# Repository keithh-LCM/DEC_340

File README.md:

Mostly eagle files, an xtra folder has extra documents.

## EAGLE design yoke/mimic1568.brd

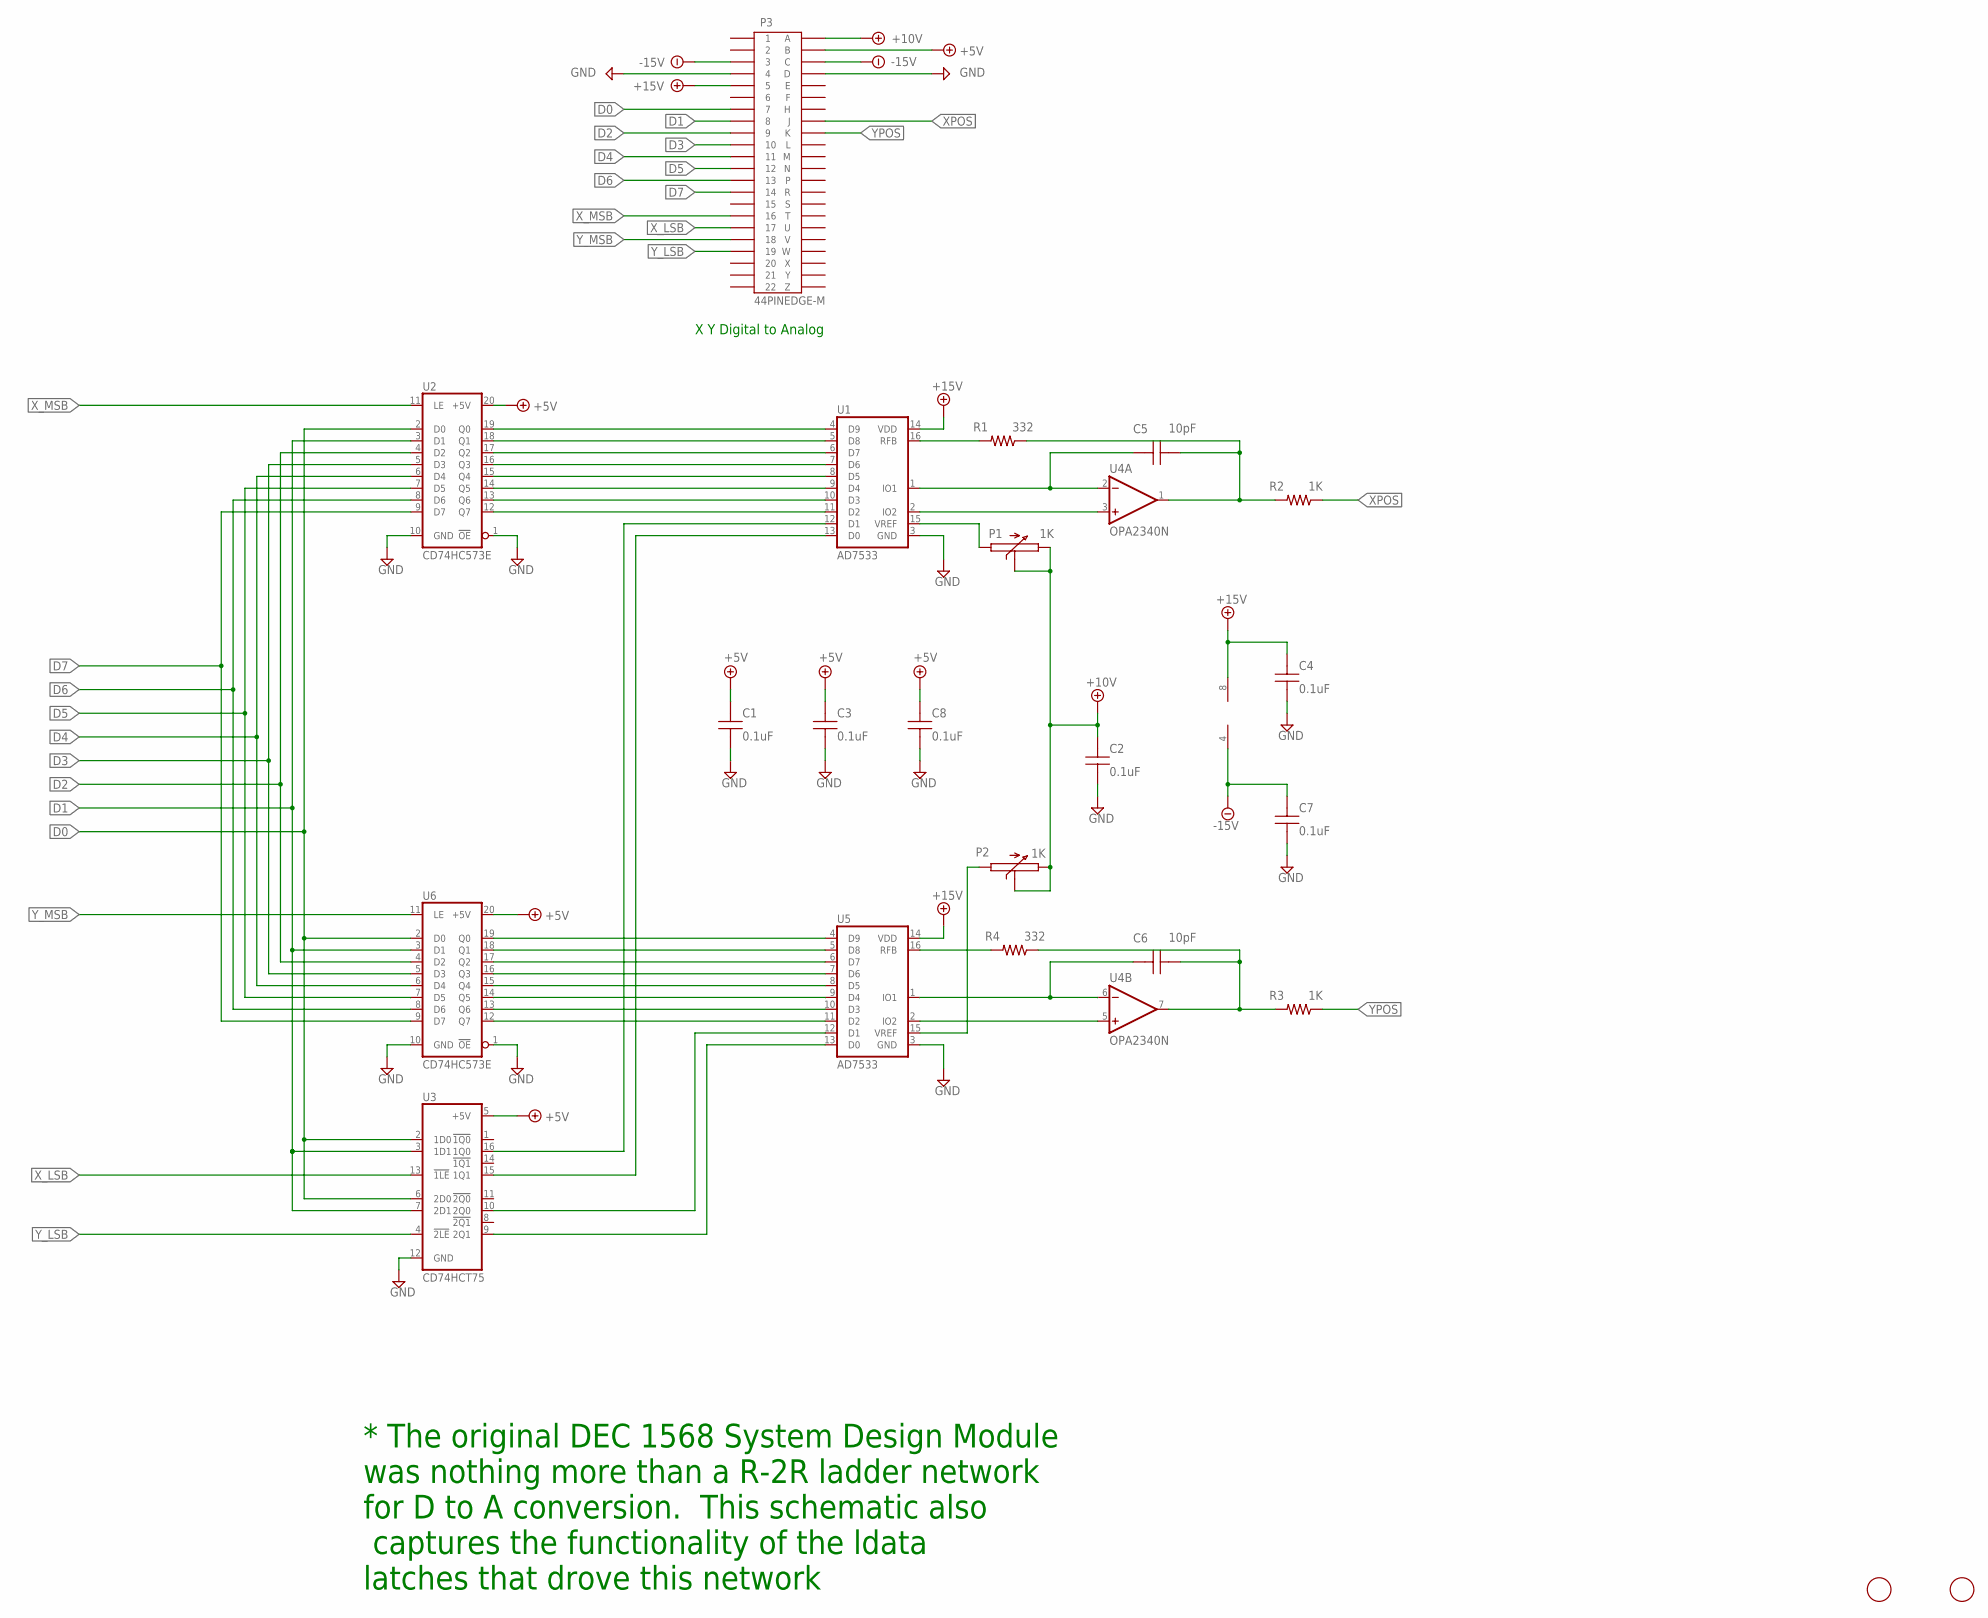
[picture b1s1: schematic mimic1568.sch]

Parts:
C1, C2, C3, C4, C7, C8: 0.1uF; 5MM_TH
C5, C6: 10pF; 5MM_TH
P1, P2: 1K; 3006P
P3: 44PINEDGE-M; 44PINEDGE
R1, R4: 332; 0207/10
R2, R3: 1K; 0207/10
U1, U5: AD7533; DIP-16
U2, U6: CD74HC573E; DIP-20
U3: CD74HCT75; DIP-16
U4: OPA2340N; DIP-08
U$1, U$2: FIDUCIAL; FIDUCIAL_1MM

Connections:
+5V: C1.1, C3.1, C8.1, P3.B, U2.20 (+5V), U3.5 (+5V), U6.20 (+5V)
+10V: C2.1, P1.2, P1.3, P2.2, P2.3, P3.A
+15V: C4.1, P3.5, U1.14 (VDD), U4.8 (V+), U5.14 (VDD)
-15V: C7.1, P3.3, P3.C, U4.4 (V-)
D0: P3.7, U2.2 (D0), U3.2 (1D0), U3.6 (2D0), U6.2 (D0)
D1: P3.8, U2.3 (D1), U3.3 (1D1), U3.7 (2D1), U6.3 (D1)
D2: P3.9, U2.4 (D2), U6.4 (D2)
D3: P3.10, U2.5 (D3), U6.5 (D3)
D4: P3.11, U2.6 (D4), U6.6 (D4)
D5: P3.12, U2.7 (D5), U6.7 (D5)
D6: P3.13, U2.8 (D6), U6.8 (D6)
D7: P3.14, U2.9 (D7), U6.9 (D7)
GND: C1.2, C2.2, C3.2, C4.2, C7.2, C8.2, P3.4, P3.D, U1.3 (GND), U2.1 (!OE), U2.10 (GND), U3.12 (GND), U5.3 (GND), U6.1 (!OE), U6.10 (GND)
unnamed: U3.9 (2Q1), U5.13 (D0)
unnamed: R4.2, U5.16 (RFB)
unnamed: U1.12 (D1), U3.16 (1Q0)
unnamed: U1.13 (D0), U3.15 (1Q1)
unnamed: C5.1, U1.1 (IO1), U4.2 (-IN)
unnamed: U1.2 (IO2), U4.3 (+IN)
unnamed: U5.4 (D9), U6.19 (Q0)
unnamed: U5.5 (D8), U6.18 (Q1)
unnamed: U5.6 (D7), U6.17 (Q2)
unnamed: U5.7 (D6), U6.16 (Q3)
unnamed: U5.8 (D5), U6.15 (Q4)
unnamed: U5.9 (D4), U6.14 (Q5)
unnamed: U5.10 (D3), U6.13 (Q6)
unnamed: U5.11 (D2), U6.12 (Q7)
unnamed: C5.2, R1.1, R2.2, U4.1 (OUT)
unnamed: P1.1, U1.15 (VREF)
unnamed: U1.4 (D9), U2.19 (Q0)
unnamed: U1.5 (D8), U2.18 (Q1)
unnamed: U1.6 (D7), U2.17 (Q2)
unnamed: U1.7 (D6), U2.16 (Q3)
unnamed: U1.8 (D5), U2.15 (Q4)
unnamed: U1.9 (D4), U2.14 (Q5)
unnamed: U1.10 (D3), U2.13 (Q6)
unnamed: U1.11 (D2), U2.12 (Q7)
unnamed: U3.10 (2Q0), U5.12 (D1)
unnamed: R1.2, U1.16 (RFB)
unnamed: C6.2, R3.2, R4.1, U4.7 (OUT)
unnamed: C6.1, U4.6 (-IN), U5.1 (IO1)
unnamed: U4.5 (+IN), U5.2 (IO2)
unnamed: P2.1, U5.15 (VREF)
XPOS: P3.J, R2.1
X_LSB: P3.17, U3.13 (!1LE)
X_MSB: P3.16, U2.11 (LE)
YPOS: P3.K, R3.1
Y_LSB: P3.19, U3.4 (!2LE)
Y_MSB: P3.18, U6.11 (LE)

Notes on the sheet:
* The original DEC 1568 System Design Module was nothing more than a R-2R ladder network for D to A conversion. This schematic also captures the functionality of the ldata latches that drove this network
X Y Digital to Analog

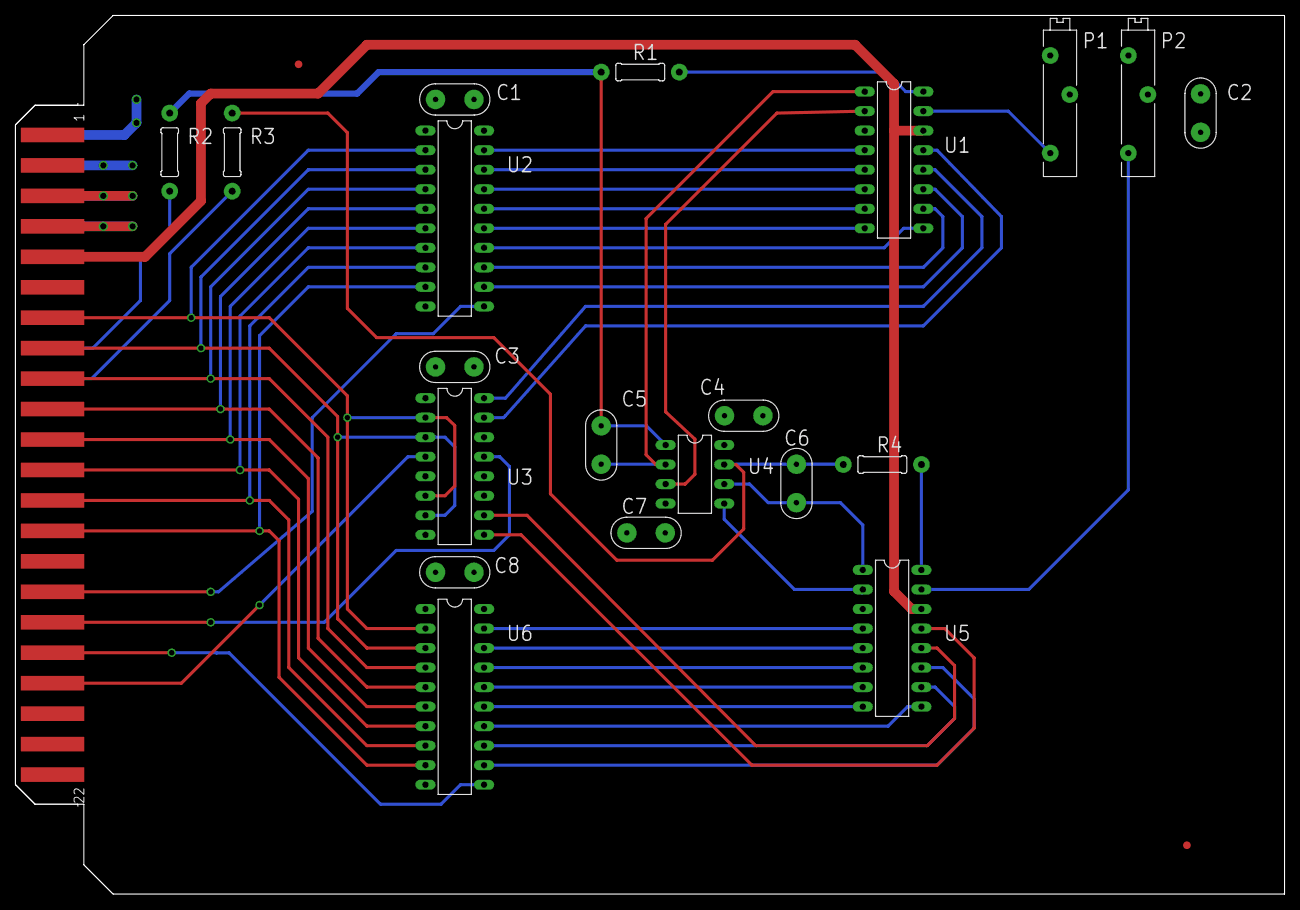
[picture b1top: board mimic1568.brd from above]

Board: 4 copper layers, 165.1 x 114.3 mm, 23 parts (0 on the bottom side), 49 nets.

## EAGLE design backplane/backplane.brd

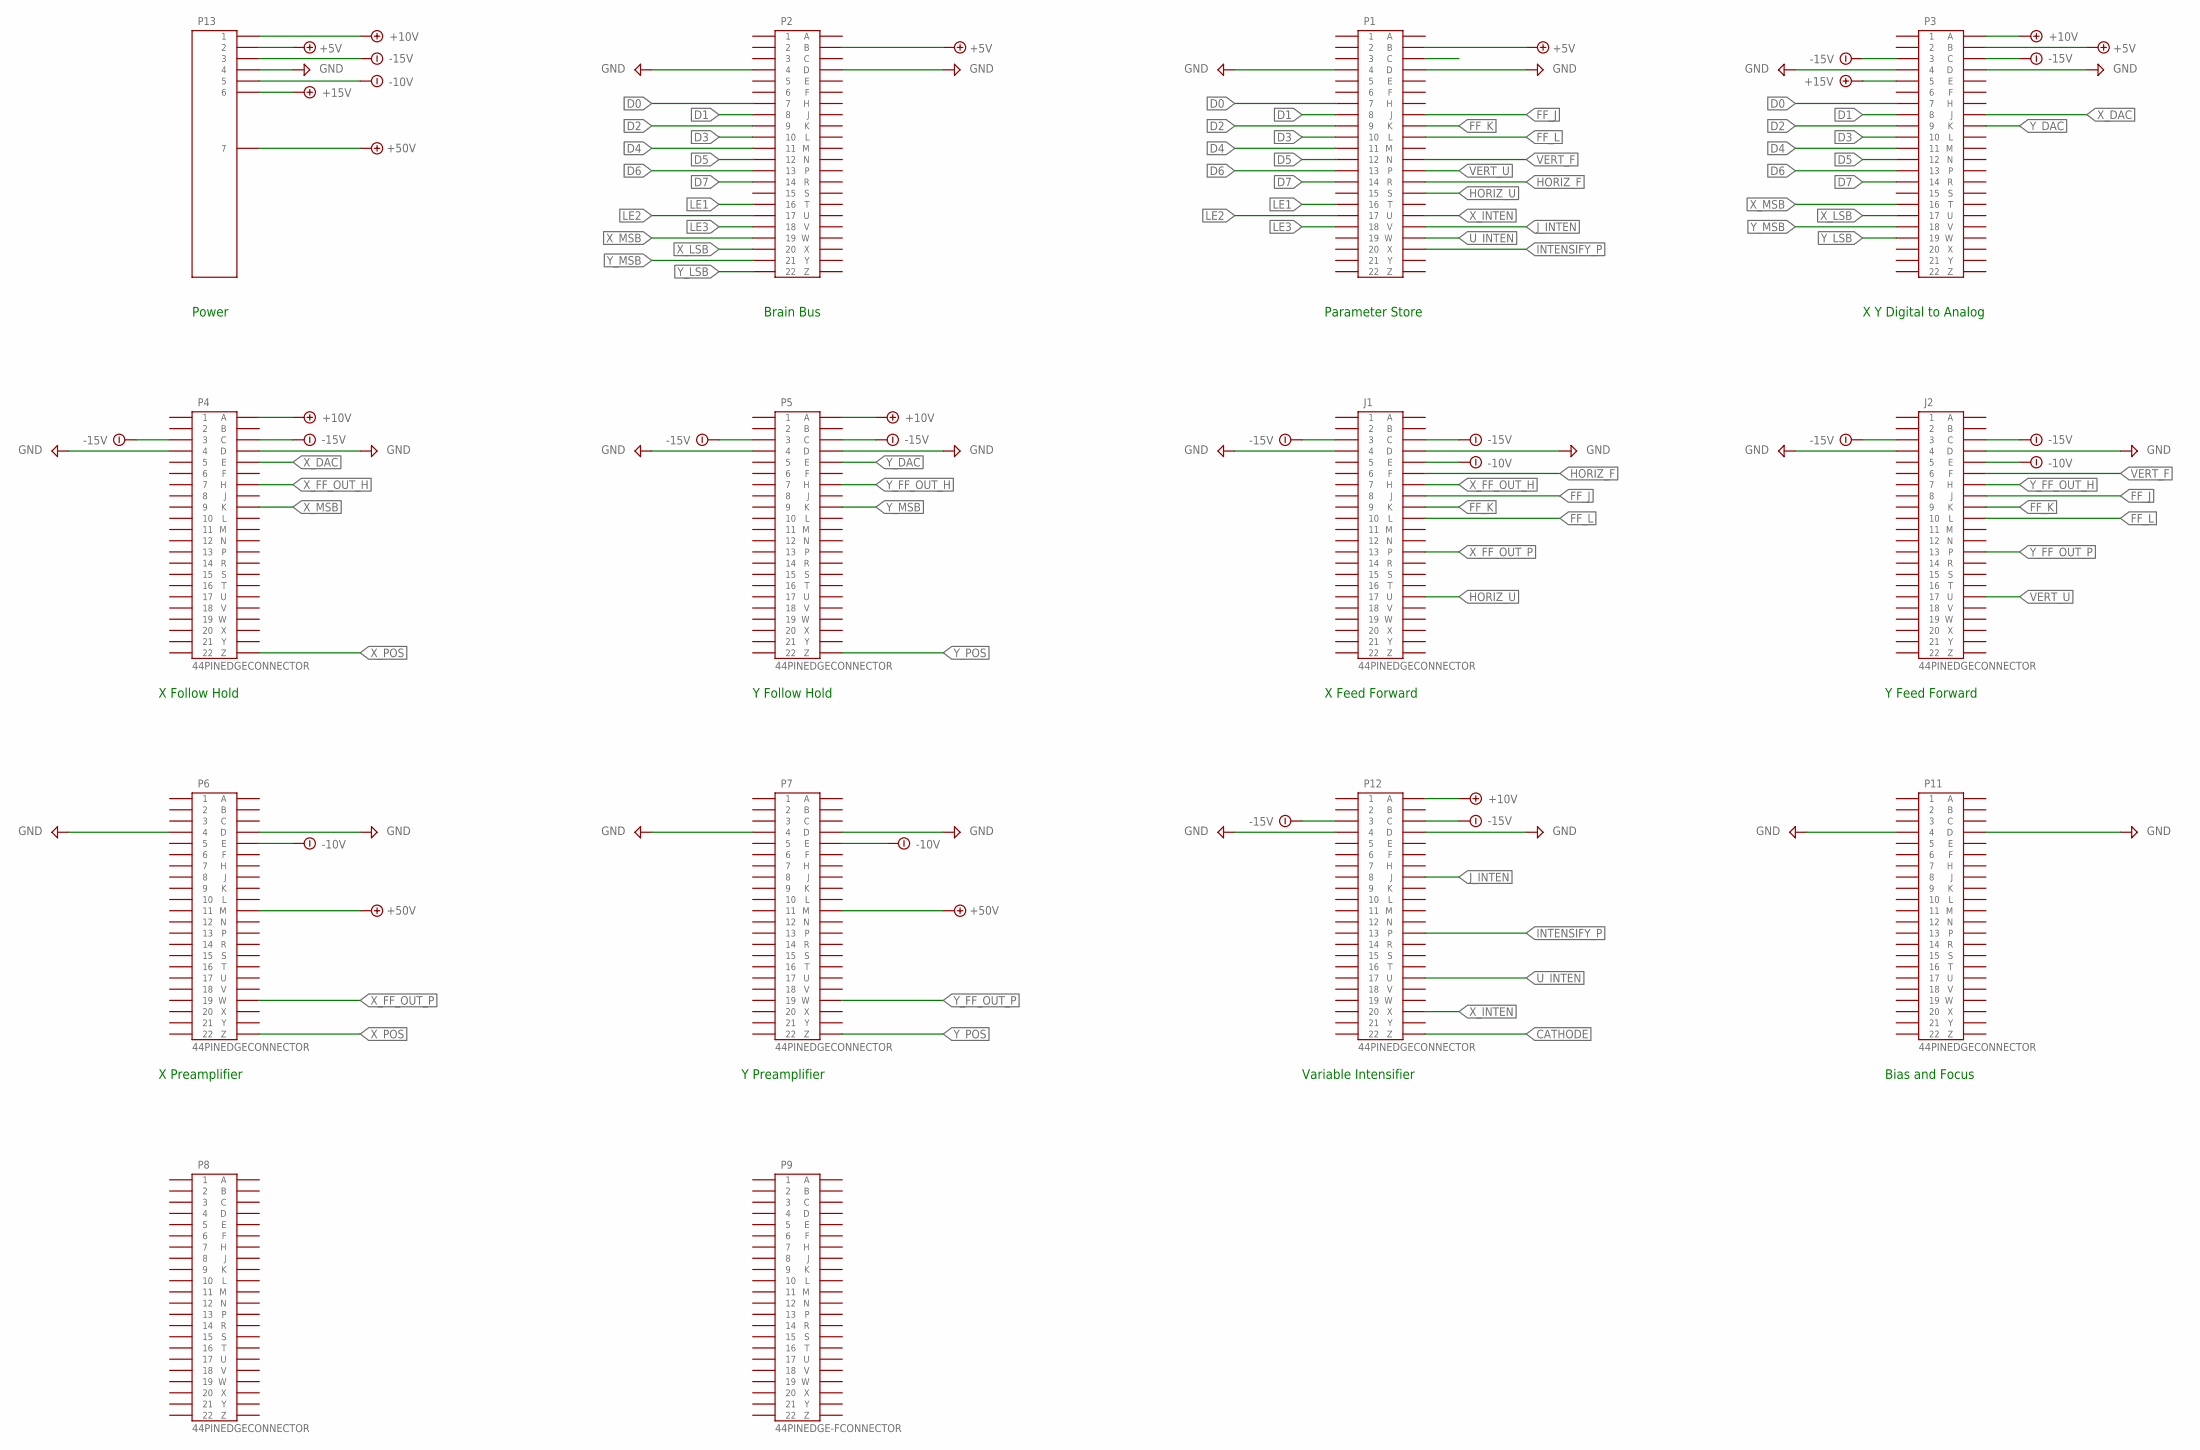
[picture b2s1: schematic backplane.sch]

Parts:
J1, J2: 44PINEDGECONNECTOR; 44PINEDGECONN
P1, P2, P3, P4, P5, P6, P7, P8, P11, P12: 44PINEDGECONNECTOR; 44PINEDGECONN
P9: 44PINEDGE-FCONNECTOR; 44PINEDGECONN
P13: PASSTHROUGH

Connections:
+5V: P1.P$24 (B), P2.P$24 (B), P3.P$24 (B), P13.P$2 (2)
+10V: P3.P$23 (A), P4.P$23 (A), P5.P$23 (A), P12.P$23 (A), P13.P$1 (1)
+15V: P3.P$5 (5), P13.P$6 (6)
+50V: P6.P$33 (M), P7.P$33 (M), P13.P$7 (7)
-10V: J1.P$27 (E), J2.P$27 (E), P6.P$27 (E), P7.P$27 (E), P13.P$5 (5)
-15V: J1.P$3 (3), J1.P$25 (C), J2.P$3 (3), J2.P$25 (C), P3.P$3 (3), P3.P$25 (C), P4.P$3 (3), P4.P$25 (C), P5.P$3 (3), P5.P$25 (C), P12.P$3 (3), P12.P$25 (C), P13.P$3 (3)
CATHODE: P12.P$44 (Z)
D0: P1.P$7 (7), P2.P$7 (7), P3.P$7 (7)
D1: P1.P$8 (8), P2.P$8 (8), P3.P$8 (8)
D2: P1.P$9 (9), P2.P$9 (9), P3.P$9 (9)
D3: P1.P$10 (10), P2.P$10 (10), P3.P$10 (10)
D4: P1.P$11 (11), P2.P$11 (11), P3.P$11 (11)
D5: P1.P$12 (12), P2.P$12 (12), P3.P$12 (12)
D6: P1.P$13 (13), P2.P$13 (13), P3.P$13 (13)
D7: P1.P$14 (14), P2.P$14 (14), P3.P$14 (14)
FF_J: J1.P$30 (J), J2.P$30 (J), P1.P$30 (J)
FF_K: J1.P$31 (K), J2.P$31 (K), P1.P$31 (K)
FF_L: J1.P$32 (L), J2.P$32 (L), P1.P$32 (L)
GND: J1.P$4 (4), J1.P$26 (D), J2.P$4 (4), J2.P$26 (D), P1.P$4 (4), P1.P$26 (D), P2.P$4 (4), P2.P$26 (D), P3.P$4 (4), P3.P$26 (D), P4.P$4 (4), P4.P$26 (D), P5.P$4 (4), P5.P$26 (D), P6.P$4 (4), P6.P$26 (D), P7.P$4 (4), P7.P$26 (D), P11.P$4 (4), P11.P$26 (D), P12.P$4 (4), P12.P$26 (D), P13.P$4 (4)
HORIZ_F: J1.P$28 (F), P1.P$36 (R)
HORIZ_U: J1.P$39 (U), P1.P$37 (S)
INTENSIFY_P: P1.P$42 (X), P12.P$35
J_INTEN: P1.P$40 (V), P12.P$30 (J)
LE1: P1.P$16 (16), P2.P$16 (16)
LE2: P1.P$17 (17), P2.P$17 (17)
LE3: P1.P$18 (18), P2.P$18 (18)
U_INTEN: P1.P$41 (W), P12.P$39 (U)
VERT_F: J2.P$28 (F), P1.P$34 (N)
VERT_U: J2.P$39 (U), P1.P$35
X_DAC: P3.P$30 (J), P4.P$27 (E)
X_FF_OUT_H: J1.P$29 (H), P4.P$29 (H)
X_FF_OUT_P: J1.P$35, P6.P$41 (W)
X_INTEN: P1.P$39 (U), P12.P$42 (X)
X_LSB: P2.P$20 (20), P3.P$17 (17)
X_MSB: P2.P$19 (19), P3.P$16 (16), P4.P$31 (K)
X_POS: P4.P$44 (Z), P6.P$44 (Z)
Y_DAC: P3.P$31 (K), P5.P$27 (E)
Y_FF_OUT_H: J2.P$29 (H), P5.P$29 (H)
Y_FF_OUT_P: J2.P$35, P7.P$41 (W)
Y_LSB: P2.P$22 (22), P3.P$19 (19)
Y_MSB: P2.P$21 (21), P3.P$18 (18), P5.P$31 (K)
Y_POS: P5.P$44 (Z), P7.P$44 (Z)

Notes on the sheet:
Brain Bus
Parameter Store
X Y Digital to Analog
X Follow Hold
Y Follow Hold
X Feed Forward
Y Feed Forward
X Preamplifier
Y Preamplifier
Variable Intensifier
Bias and Focus
Power

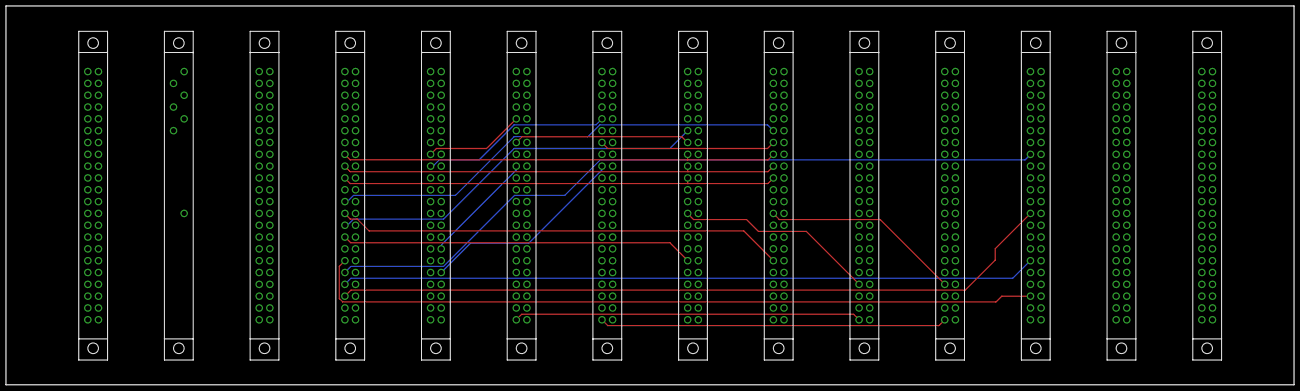
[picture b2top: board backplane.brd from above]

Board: 6 copper layers, 431.8 x 127.0 mm, 14 parts (0 on the bottom side), 41 nets.

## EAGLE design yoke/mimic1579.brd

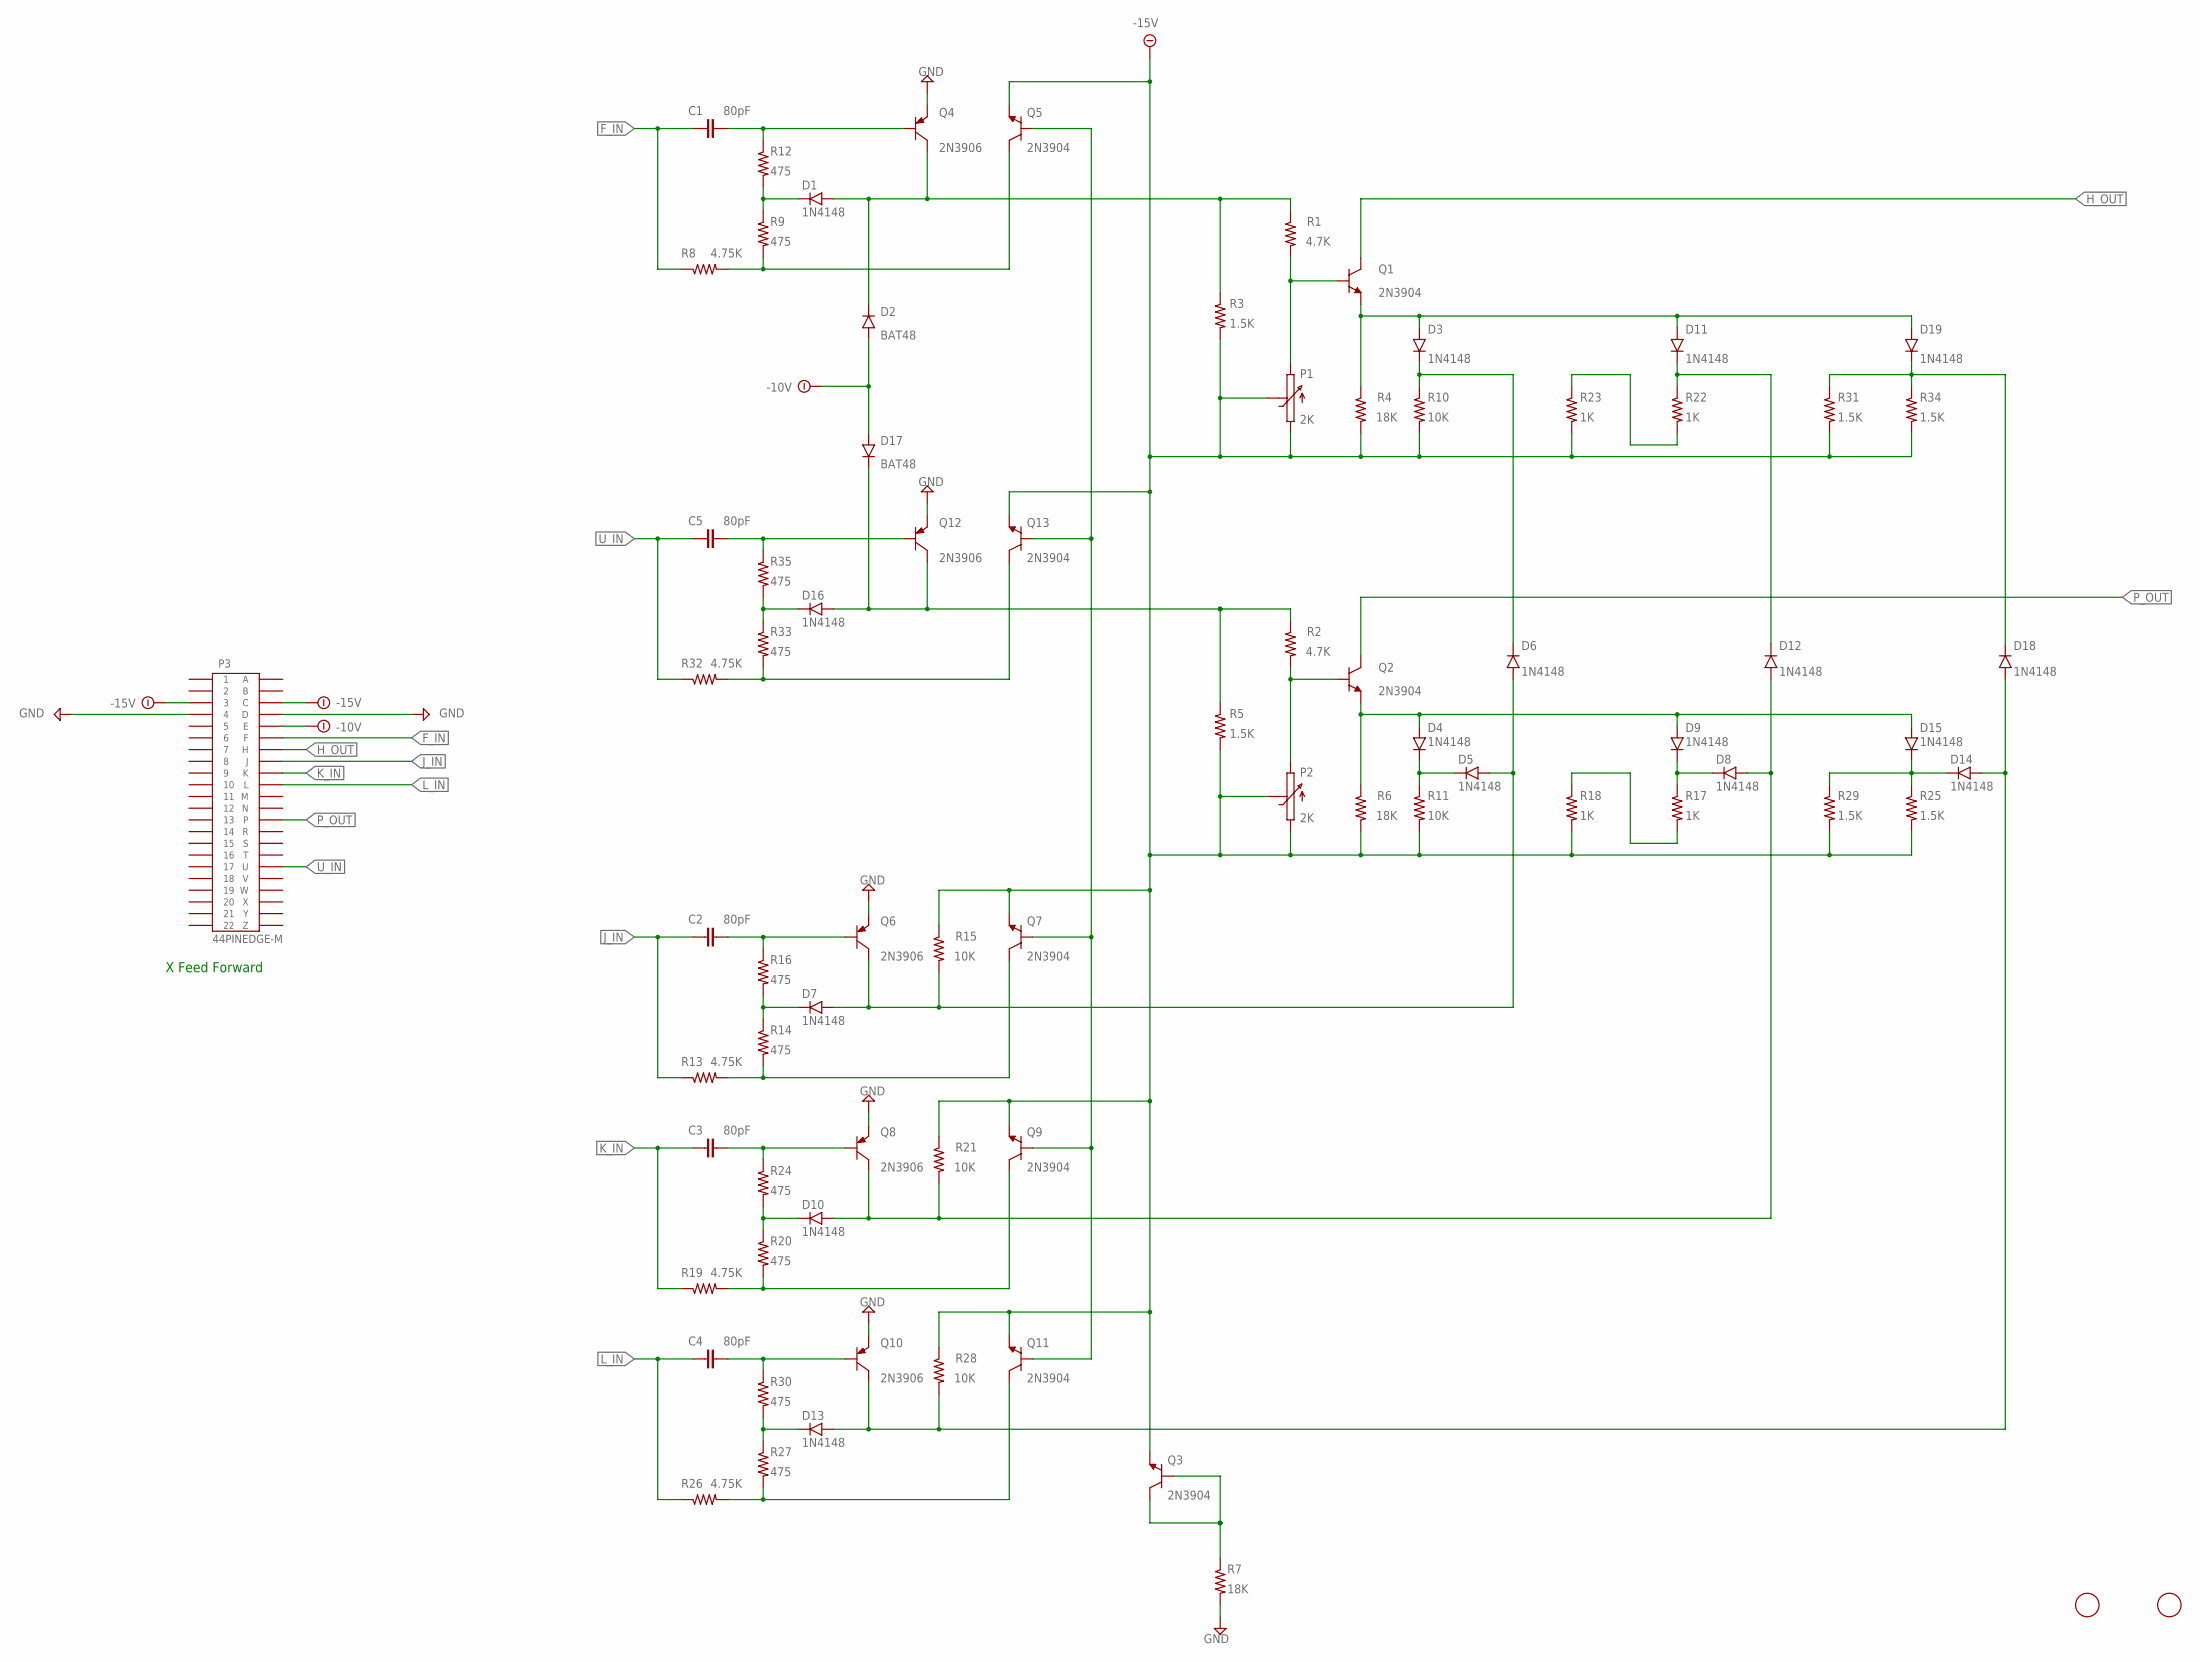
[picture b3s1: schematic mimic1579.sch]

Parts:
C1, C2, C3, C4, C5: 80pF; 5MM_TH
D1, D3, D4, D5, D6, D7, D8, D9, D10, D11, D12, D13, D14, D15, D16, D18, D19: 1N4148; DO35-7
D2, D17: BAT48; DO35-7
P1, P2: 2K; 3006P
P3: 44PINEDGE-M; 44PINEDGE
Q1, Q2, Q3, Q5, Q7, Q9, Q11, Q13: 2N3904; TO92
Q4, Q6, Q8, Q10, Q12: 2N3906; TO92
R1, R2: 4.7K; 0207/10
R3, R5, R25, R29, R31, R34: 1.5K; 0207/10
R4, R6, R7: 18K; 0207/10
R8, R13, R19, R26, R32: 4.75K; 0207/10
R9, R12, R14, R16, R20, R24, R27, R30, R33, R35: 475; 0207/10
R10, R11, R15, R21, R28: 10K; 0207/10
R17, R18, R22, R23: 1K; 0207/10
U$1, U$2: FIDUCIAL; FIDUCIAL_1MM

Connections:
-10V: D2.A, D17.A, P3.E
-15V: P1.1, P1.2, P2.1, P2.2, P3.3, P3.C, Q3.1 (E), Q5.1 (E), Q7.1 (E), Q9.1 (E), Q11.1 (E), Q13.1 (E), R3.2, R4.2, R5.2, R6.2, R10.2, R11.2, R15.1, R18.2, R21.1, R23.2, R25.2, R28.1, R29.2, R31.2, R34.2
F_IN: C1.1, P3.F, R8.1
GND: P3.4, P3.D, Q4.3 (E), Q6.3 (E), Q8.3 (E), Q10.3 (E), Q12.3 (E), R7.2
H_OUT: P3.H, Q1.3 (C)
J_IN: C2.1, P3.J, R13.1
K_IN: C3.1, P3.K, R19.1
L_IN: C4.1, P3.L, R26.1
unnamed: C1.2, Q4.2 (B), R12.1
unnamed: Q5.3 (C), R8.2, R9.2
unnamed: C3.2, Q8.2 (B), R24.1
unnamed: P1.3, Q1.2 (B), R1.2
unnamed: D3.A, D11.A, D19.A, Q1.1 (E), R4.1
unnamed: D3.C, D6.C, R10.1
unnamed: R22.2, R23.1
unnamed: Q9.3 (C), R19.2, R20.2
unnamed: D1.C, R9.1, R12.2
unnamed: D11.C, D12.C, R22.1
unnamed: D18.C, D19.C, R31.1, R34.1
unnamed: D10.C, R20.1, R24.2
unnamed: C4.2, Q10.2 (B), R30.1
unnamed: C5.2, Q12.2 (B), R35.1
unnamed: Q13.3 (C), R32.2, R33.2
unnamed: P2.3, Q2.2 (B), R2.2
unnamed: D4.A, D9.A, D15.A, Q2.1 (E), R6.1
unnamed: D4.C, D5.C, R11.1
unnamed: D8.C, D9.C, R17.1
unnamed: R17.2, R18.1
unnamed: D14.C, D15.C, R25.1, R29.1
unnamed: Q11.3 (C), R26.2, R27.2
unnamed: D13.C, R27.1, R30.2
unnamed: Q3.2 (B), Q3.3 (C), R7.1
unnamed: D16.C, R33.1, R35.2
unnamed: C2.2, Q6.2 (B), R16.1
unnamed: Q7.3 (C), R13.2, R14.2
unnamed: D7.C, R14.1, R16.2
unnamed: Q5.2 (B), Q7.2 (B), Q9.2 (B), Q11.2 (B), Q13.2 (B)
P_OUT: P3.P, Q2.3 (C)
U_IN: C5.1, P3.U, R32.1
VREF: D1.A, D2.C, Q4.1 (C), R1.1, R3.1
VREF1: D8.A, D10.A, D12.A, Q8.1 (C), R21.2
VREF2: D13.A, D14.A, D18.A, Q10.1 (C), R28.2
VREF3: D5.A, D6.A, D7.A, Q6.1 (C), R15.2
VREF5: D16.A, D17.C, Q12.1 (C), R2.1, R5.1

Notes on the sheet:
X Feed Forward

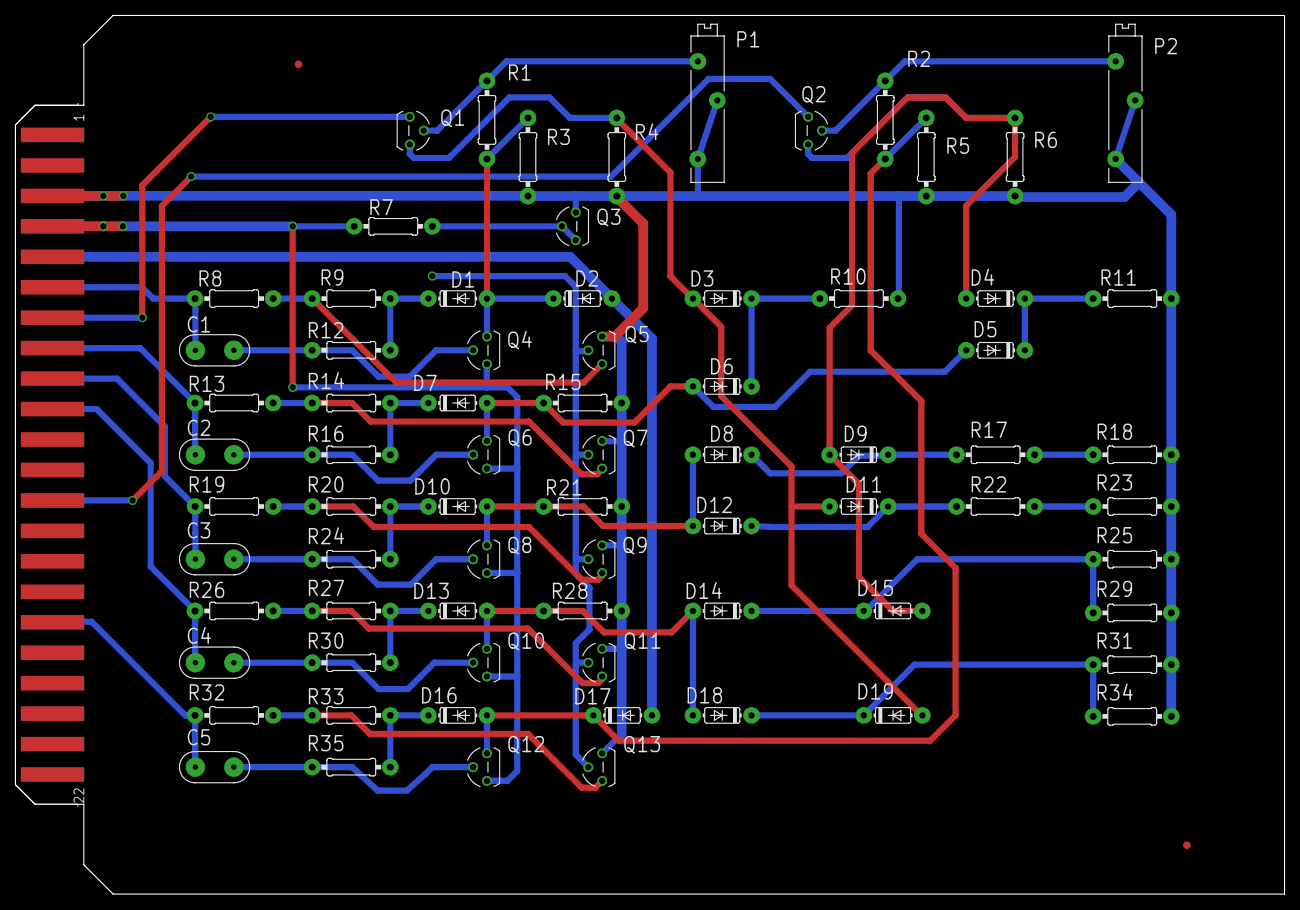
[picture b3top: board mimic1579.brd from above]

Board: 2 copper layers, 165.1 x 114.3 mm, 77 parts (0 on the bottom side), 44 nets.

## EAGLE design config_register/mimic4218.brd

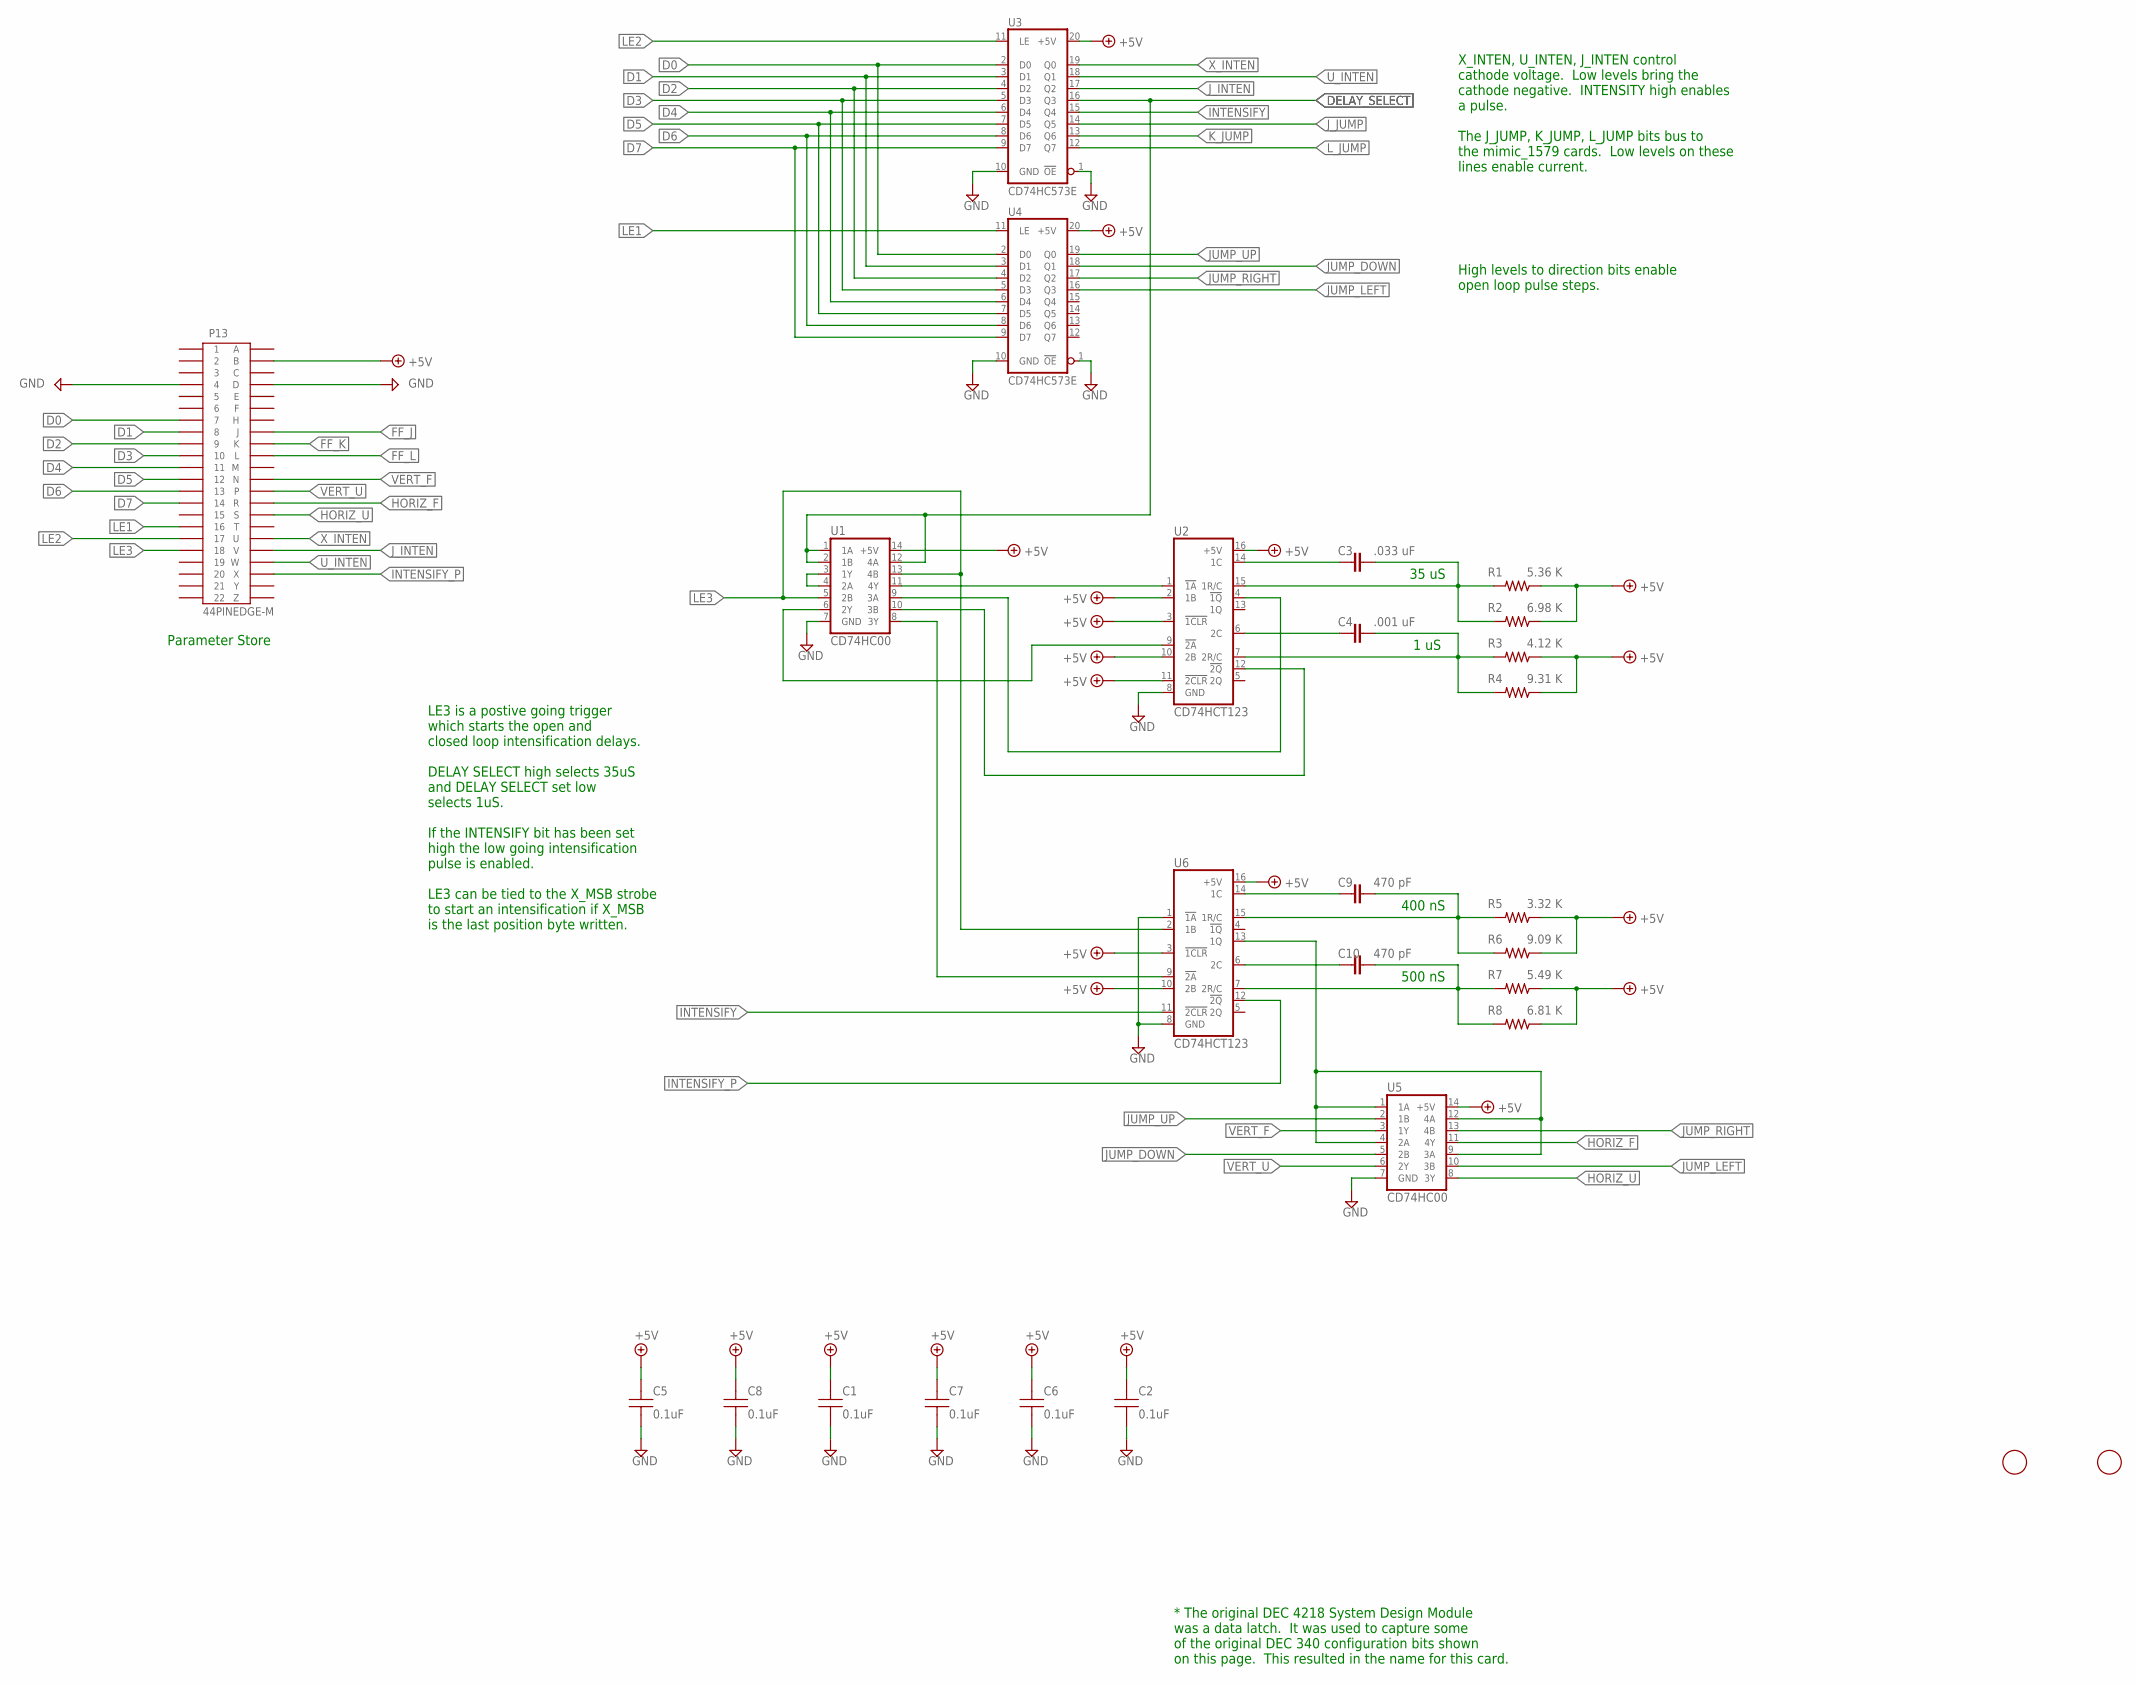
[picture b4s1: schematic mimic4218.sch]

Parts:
C1, C2, C5, C6, C7, C8: 0.1uF; 5MM_TH
C3: .033 uF; 5MM_TH
C4: .001 uF; 5MM_TH
C9, C10: 470 pF; 5MM_TH
P13: 44PINEDGE-M; 44PINEDGE
R1: 5.36 K; 0207/10
R2: 6.98 K; 0207/10
R3: 4.12 K; 0207/10
R4: 9.31 K; 0207/10
R5: 3.32 K; 0207/10
R6: 9.09 K; 0207/10
R7: 5.49 K; 0207/10
R8: 6.81 K; 0207/10
U1, U5: CD74HC00; DIP-14
U2, U6: CD74HCT123; DIP-16
U3, U4: CD74HC573E; DIP-20
U$1, U$2: FIDUCIAL; FIDUCIAL_1MM

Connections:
+5V: C1.1, C2.1, C5.1, C6.1, C7.1, C8.1, P13.B, R1.1, R2.1, R3.1, R4.1, R5.1, R6.1, R7.1, R8.1, U1.14 (+5V), U2.2 (1B), U2.3 (!1CLR), U2.10 (2B), U2.11 (!2CLR), U2.16 (+5V), U3.20 (+5V), U4.20 (+5V), U5.14 (+5V), U6.3 (!1CLR), U6.10 (2B), U6.16 (+5V)
D0: P13.7, U3.2 (D0), U4.2 (D0)
D1: P13.8, U3.3 (D1), U4.3 (D1)
D2: P13.9, U3.4 (D2), U4.4 (D2)
D3: P13.10, U3.5 (D3), U4.5 (D3)
D4: P13.11, U3.6 (D4), U4.6 (D4)
D5: P13.12, U3.7 (D5), U4.7 (D5)
D6: P13.13, U3.8 (D6), U4.8 (D6)
D7: P13.14, U3.9 (D7), U4.9 (D7)
DELAY_SELECT: U1.1 (1A), U1.2 (1B), U1.12 (4A), U3.16 (Q3)
FF_J: P13.J
FF_K: P13.K
FF_L: P13.L
GND: C1.2, C2.2, C5.2, C6.2, C7.2, C8.2, P13.4, P13.D, U1.7 (GND), U2.8 (GND), U3.1 (!OE), U3.10 (GND), U4.1 (!OE), U4.10 (GND), U5.7 (GND), U6.1 (!1A), U6.8 (GND)
HORIZ_F: P13.R, U5.11 (4Y)
HORIZ_U: P13.S, U5.8 (3Y)
INTENSIFY: U3.15 (Q4), U6.11 (!2CLR)
INTENSIFY_P: P13.X, U6.12 (!2Q)
JUMP_DOWN: U4.18 (Q1), U5.5 (2B)
JUMP_LEFT: U4.16 (Q3), U5.10 (3B)
JUMP_RIGHT: U4.17 (Q2), U5.13 (4B)
JUMP_UP: U4.19 (Q0), U5.2 (1B)
J_INTEN: P13.V, U3.17 (Q2)
J_JUMP: U3.14 (Q5)
K_JUMP: U3.13 (Q6)
LE1: P13.16, U4.11 (LE)
LE2: P13.17, U3.11 (LE)
LE3: P13.18, U1.5 (2B), U1.13 (4B), U6.2 (1B)
L_JUMP: U3.12 (Q7)
unnamed: C3.1, U2.14 (1C)
unnamed: C3.2, R1.2, R2.2, U2.15 (1R/C)
unnamed: C4.1, U2.6 (2C)
unnamed: C4.2, R3.2, R4.2, U2.7 (2R/C)
unnamed: C9.1, U6.14 (1C)
unnamed: C10.2, R7.2, R8.2, U6.7 (2R/C)
unnamed: C10.1, U6.6 (2C)
unnamed: C9.2, R5.2, R6.2, U6.15 (1R/C)
unnamed: U1.11 (4Y), U2.1 (!1A)
unnamed: U1.3 (1Y), U1.4 (2A)
unnamed: U5.1 (1A), U5.4 (2A), U5.9 (3A), U5.12 (4A), U6.13 (1Q)
unnamed: U1.6 (2Y), U2.9 (!2A)
unnamed: U1.9 (3A), U2.4 (!1Q)
unnamed: U1.10 (3B), U2.12 (!2Q)
unnamed: U1.8 (3Y), U6.9 (!2A)
U_INTEN: P13.W, U3.18 (Q1)
VERT_F: P13.N, U5.3 (1Y)
VERT_U: P13.P, U5.6 (2Y)
X_INTEN: P13.U, U3.19 (Q0)

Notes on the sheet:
35 uS
1 uS
500 nS
400 nS
* The original DEC 4218 System Design Module was a data latch. It was used to capture some of the original DEC 340 configuration bits shown on this page. This resulted in the name for this card.
High levels to direction bits enable open loop pulse steps.
X_INTEN, U_INTEN, J_INTEN control cathode voltage. Low levels bring the cathode negative. INTENSITY high enables a pulse. The J_JUMP, K_JUMP, L_JUMP bits bus to the mimic_1579 cards. Low levels on these lines enable current.
LE3 is a postive going trigger which starts the open and closed loop intensification delays. DELAY SELECT high selects 35uS and DELAY SELECT set low selects 1uS. If the INTENSIFY bit has been set high the low going intensification pulse is enabled. LE3 can be tied to the X_MSB strobe to start an in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
Parameter Store
